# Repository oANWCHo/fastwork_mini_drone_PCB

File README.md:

# Mini Drone PCB
### This project was designed in KiCAD V9.0 
### If you don't have this program, you can find a schematic for review in the documents folder.

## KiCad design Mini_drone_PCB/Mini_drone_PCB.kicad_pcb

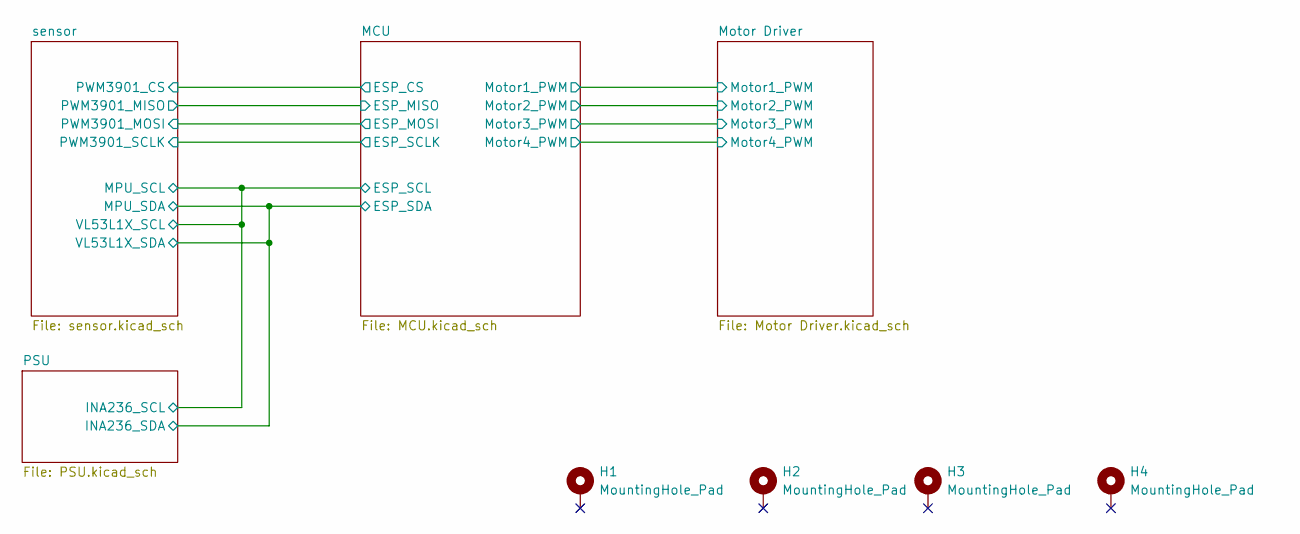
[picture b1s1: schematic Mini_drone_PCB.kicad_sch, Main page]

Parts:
H1, H2, H3, H4: MountingHole_Pad; MountingHole_2.5mm_Pad

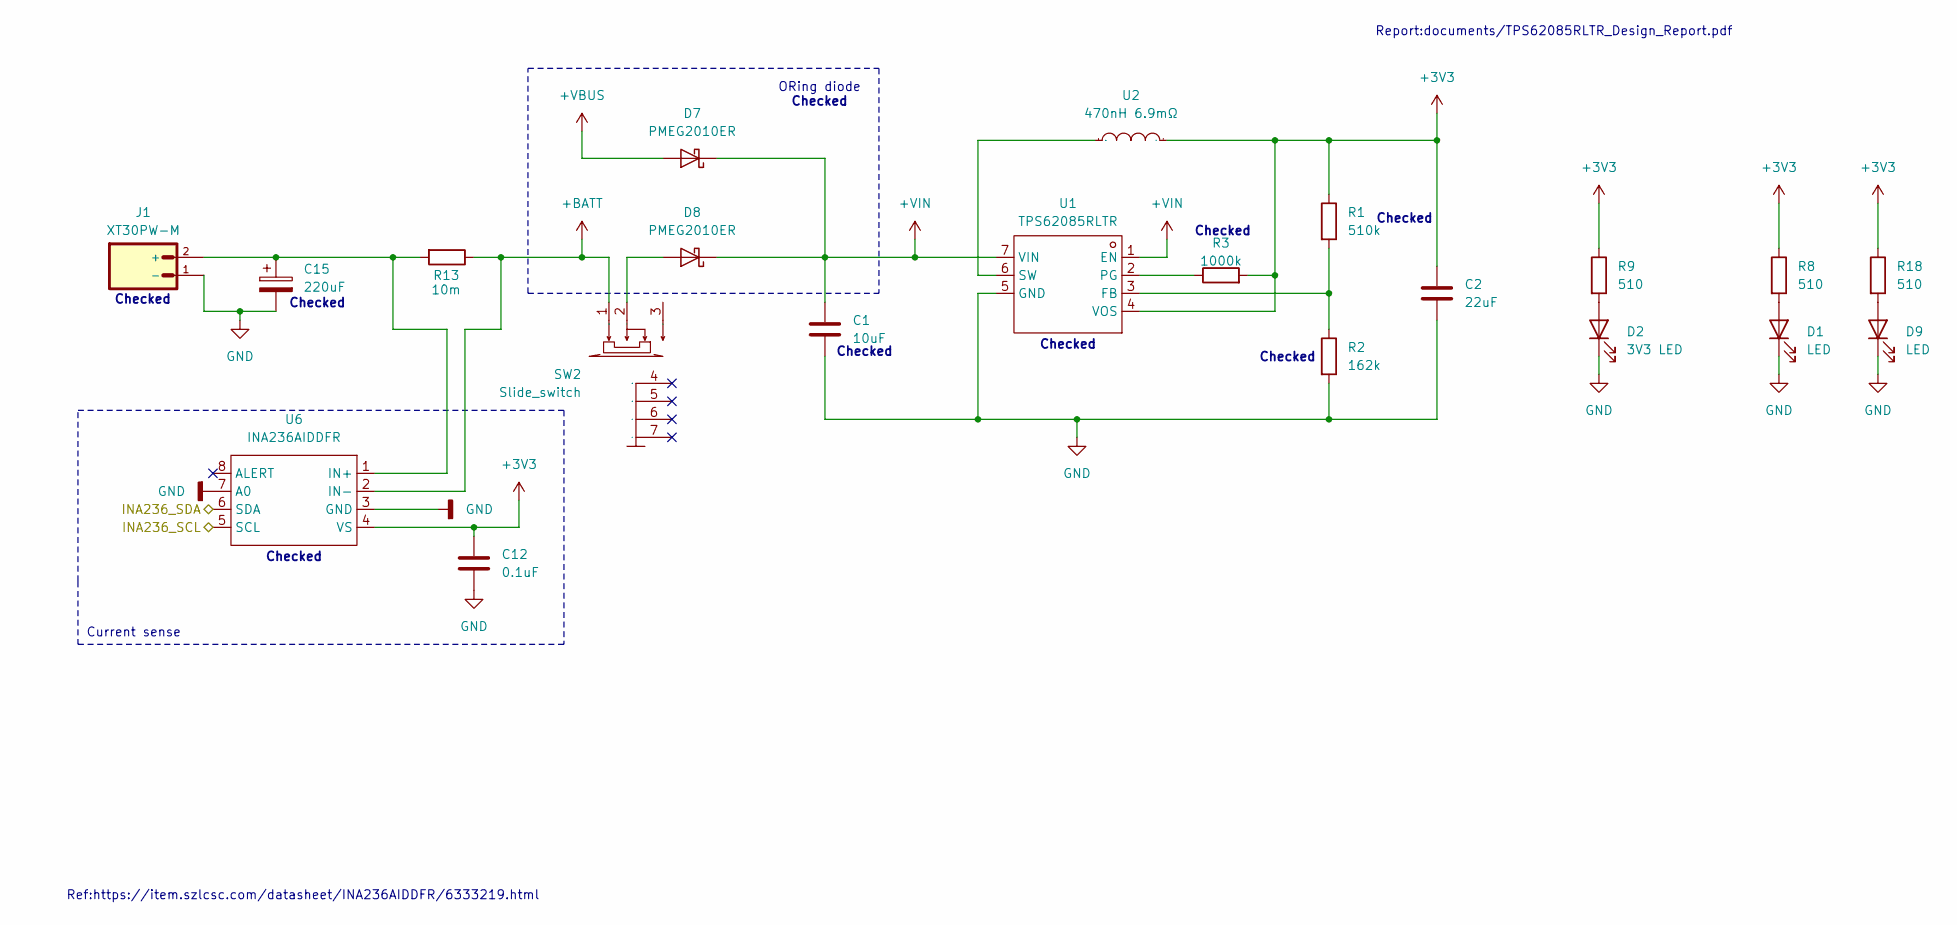
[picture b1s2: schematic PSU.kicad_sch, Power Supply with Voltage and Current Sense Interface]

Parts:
C1: 10uF; C_0402_1005Metric; LCSC Part # C15525
C2: 22uF; C_0402_1005Metric; LCSC Part # C105226
C12: 0.1uF; C_0402_1005Metric; LCSC Part # C1525
C15: 220uF; CP_Elec_6.3x5.4; LCSC Part # C72494
D1, D9: LED; LED_D3.0mm_Horizontal_O6.35mm_Z2.0mm
D2: 3V3 LED; LED_0603_1608Metric; LCSC Part # C2286
D7, D8: PMEG2010ER; Nexperia_CFP3_SOD-123W; LCSC Part # C82288
J1: XT30PW-M; AMASS_XT30PW-M; LCSC Part # C431092
R1: 510k; C_0402_1005Metric; LCSC Part # C11616
R2: 162k; C_0402_1005Metric; LCSC Part # C185462
R3: 1000k; C_0402_1005Metric; LCSC Part # C26083
R8, R9, R18: 510; C_0402_1005Metric; LCSC Part # C25123
R13: 10m; R_2512_6332Metric; LCSC Part # C105366
SW2: Slide_switch; SW-SMD_SSSS811101; Manufacturer Part SSSS811101; LCSC Part Name 1.4mm高、1.5/2.0mm行程表面贴装型开关
U1: TPS62085RLTR; VSON-7_L2.0-W2.0-P0.5-TL; Manufacturer Part TPS62085RLTR; LCSC Part Name 高效3A同步降压转换器
U2: 470nH 6.9mΩ; IND-SMD_L4.2-W4.0_SPM4030T; Manufacturer Part SPM4030T-R47M-HZ; LCSC Part Name 470nH ±20%
U6: INA236AIDDFR; SOT-23-8_L2.9-W1.6-P0.65-LS2.8-BR; Manufacturer Part INA236AIDDFR; LCSC Part Name INA236AIDDFR

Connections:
+3V3: C2.1, C12.1, R1.1, R3.2, R8.1, R9.1, R18.1, U1.4 (VOS), U2.2, U6.4 (VS); also elsewhere on the board
+BATT: R13.1, SW2.1, U6.2 (IN-); also elsewhere on the board
+VBUS: D7.2 (A); also elsewhere on the board
+VIN: C1.1, D7.1 (K), D8.1 (K), U1.1 (EN), U1.7 (VIN)
/MCU/ESP_SCL: U6.5 (SCL); also elsewhere on the board
/MCU/ESP_SDA: U6.6 (SDA); also elsewhere on the board
GND: C1.2, C2.2, C12.2, C15.2, D1.1 (K), D2.1 (K), D9.1 (K), J1.1 (-), R2.2, U1.5 (GND), U6.3 (GND), U6.7 (A0); also elsewhere on the board
unnamed: D1.2 (A), R8.2
unnamed: D2.2 (A), R9.2
unnamed: D8.2 (A), SW2.2
unnamed: D9.2 (A), R18.2
unnamed: C15.1, J1.2 (+), R13.2, U6.1 (IN+)
unnamed: R1.2, R2.1, U1.3 (FB)
unnamed: R3.1, U1.2 (PG)
unnamed: U1.6 (SW), U2.1

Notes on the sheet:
ORing diode
Checked
Current sense
Report:documents/TPS62085RLTR_Design_Report.pdf
Ref:https://item.szlcsc.com/datasheet/INA236AIDDFR/6333219.html

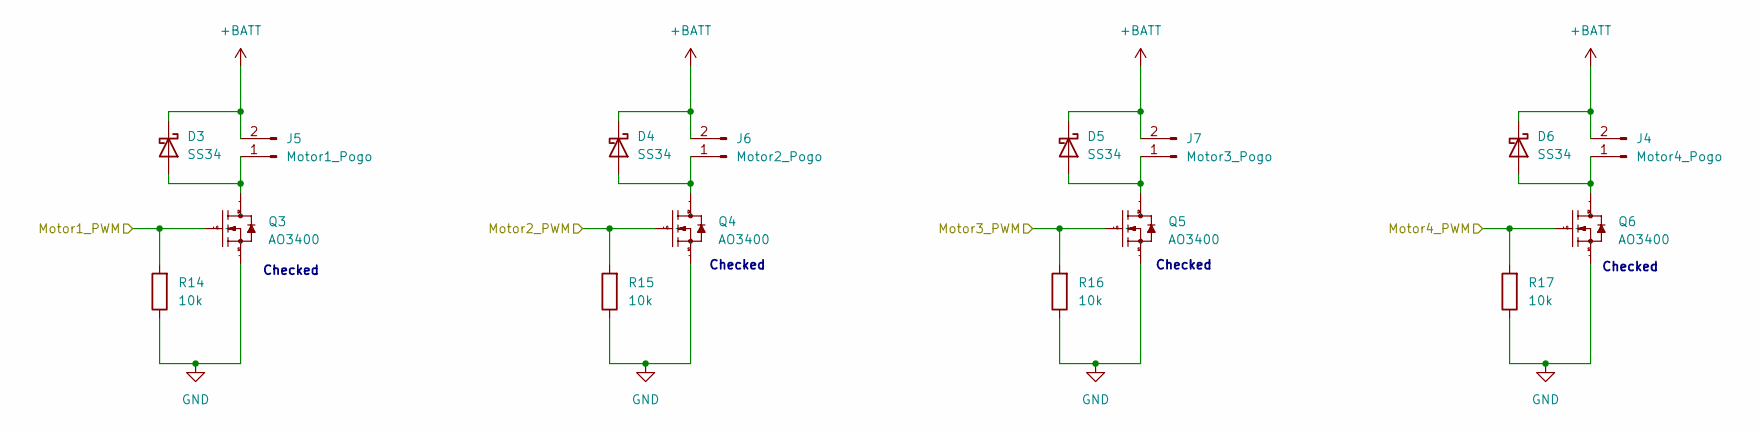
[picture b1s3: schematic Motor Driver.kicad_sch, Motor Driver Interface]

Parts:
D3, D4, D5, D6: SS34; D_SMA; LCSC Part # C8678
J4: Motor4_Pogo; POGO 2Pin Pitch 4
J5: Motor1_Pogo; POGO 2Pin Pitch 4
J6: Motor2_Pogo; POGO 2Pin Pitch 4
J7: Motor3_Pogo; POGO 2Pin Pitch 4
Q3, Q4, Q5, Q6: AO3400; SOT-23-3_L2.9-W1.3-P1.90-LS2.4-BR; Manufacturer Part AO3400; LCSC Part Name 1个N沟道 耐压:30V 电流:5.8A
R14, R15, R16, R17: 10k; C_0402_1005Metric; LCSC Part # C25531

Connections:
+BATT: D3.1 (K), D4.1 (K), D5.1 (K), D6.1 (K), J4.2, J5.2, J6.2, J7.2; also elsewhere on the board
/MCU/Motor1_PWM: Q3.1 (G), R14.2; also elsewhere on the board
/MCU/Motor2_PWM: Q4.1 (G), R15.2; also elsewhere on the board
/MCU/Motor3_PWM: Q5.1 (G), R16.2; also elsewhere on the board
/MCU/Motor4_PWM: Q6.1 (G), R17.2; also elsewhere on the board
GND: Q3.2 (S), Q4.2 (S), Q5.2 (S), Q6.2 (S), R14.1, R15.1, R16.1, R17.1; also elsewhere on the board
unnamed: D3.2 (A), J5.1, Q3.3 (D)
unnamed: D4.2 (A), J6.1, Q4.3 (D)
unnamed: D5.2 (A), J7.1, Q5.3 (D)
unnamed: D6.2 (A), J4.1, Q6.3 (D)

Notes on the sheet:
Checked

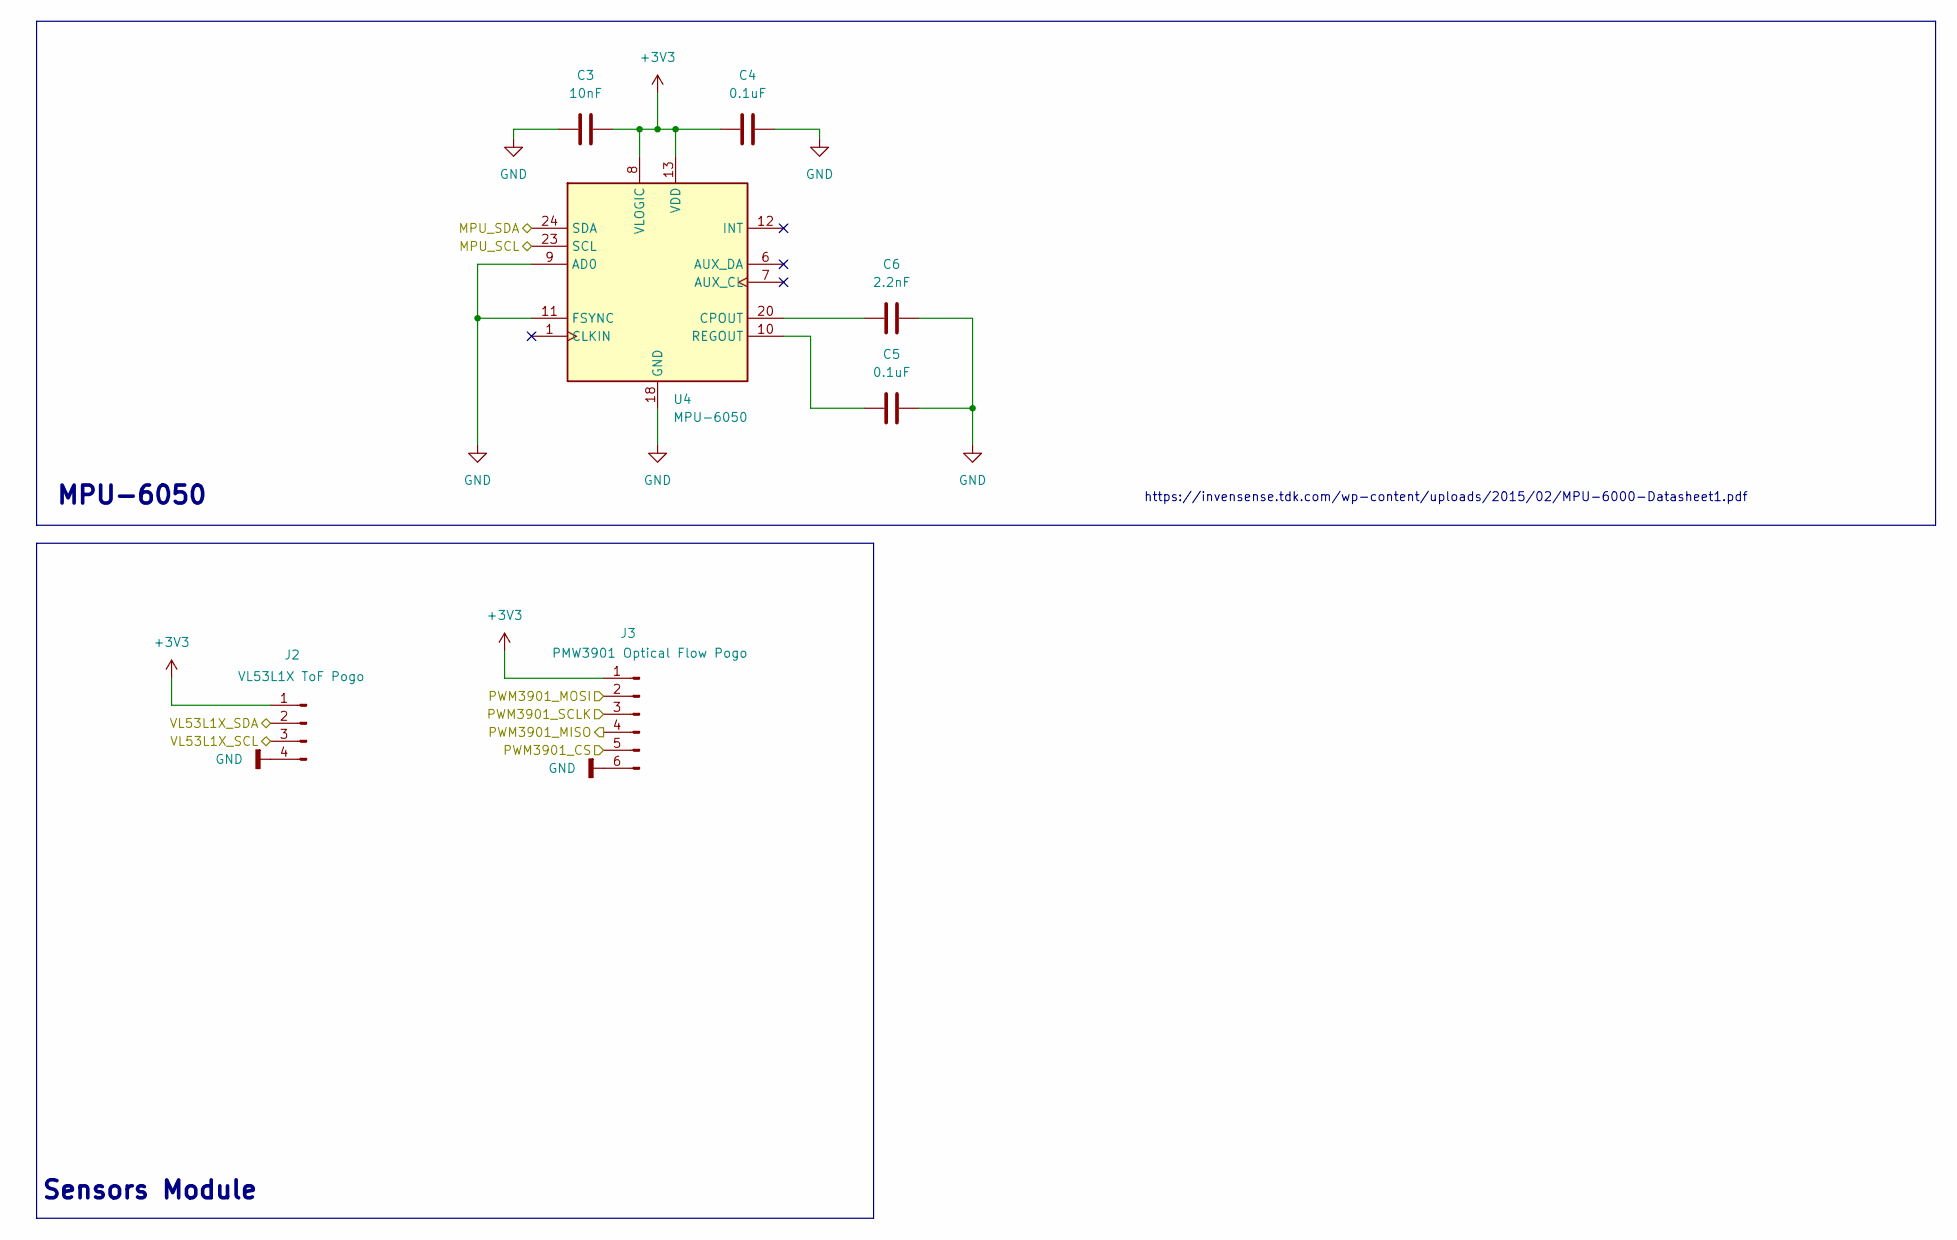
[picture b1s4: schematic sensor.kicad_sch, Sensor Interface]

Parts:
C3: 10nF; C_0402_1005Metric; LCSC Part # C15195
C4, C5: 0.1uF; C_0402_1005Metric; LCSC Part # C1525
C6: 2.2nF; C_0402_1005Metric; LCSC Part # C1531
J2: VL53L1X ToF Pogo; POGO 4Pin Pitch 2.54
J3: PMW3901 Optical Flow Pogo; POGO 6Pin Pitch 2.54
U4: MPU-6050; InvenSense_QFN-24_4x4mm_P0.5mm; LCSC Part # C24112

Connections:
+3V3: C3.1, C4.2, J2.1, J3.1, U4.8 (VLOGIC), U4.13 (VDD); also elsewhere on the board
/MCU/ESP_CS: J3.5; also elsewhere on the board
/MCU/ESP_MISO: J3.4; also elsewhere on the board
/MCU/ESP_MOSI: J3.2; also elsewhere on the board
/MCU/ESP_SCL: J2.3, U4.23 (SCL); also elsewhere on the board
/MCU/ESP_SCLK: J3.3; also elsewhere on the board
/MCU/ESP_SDA: J2.2, U4.24 (SDA); also elsewhere on the board
GND: C3.2, C4.1, C5.1, C6.1, J2.4, J3.6, U4.9 (AD0), U4.11 (FSYNC), U4.18 (GND); also elsewhere on the board
unnamed: C6.2, U4.20 (CPOUT)
unnamed: C5.2, U4.10 (REGOUT)

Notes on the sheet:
https://invensense.tdk.com/wp-content/uploads/2015/02/MPU-6000-Datasheet1.pdf
MPU-6050
Sensors Module

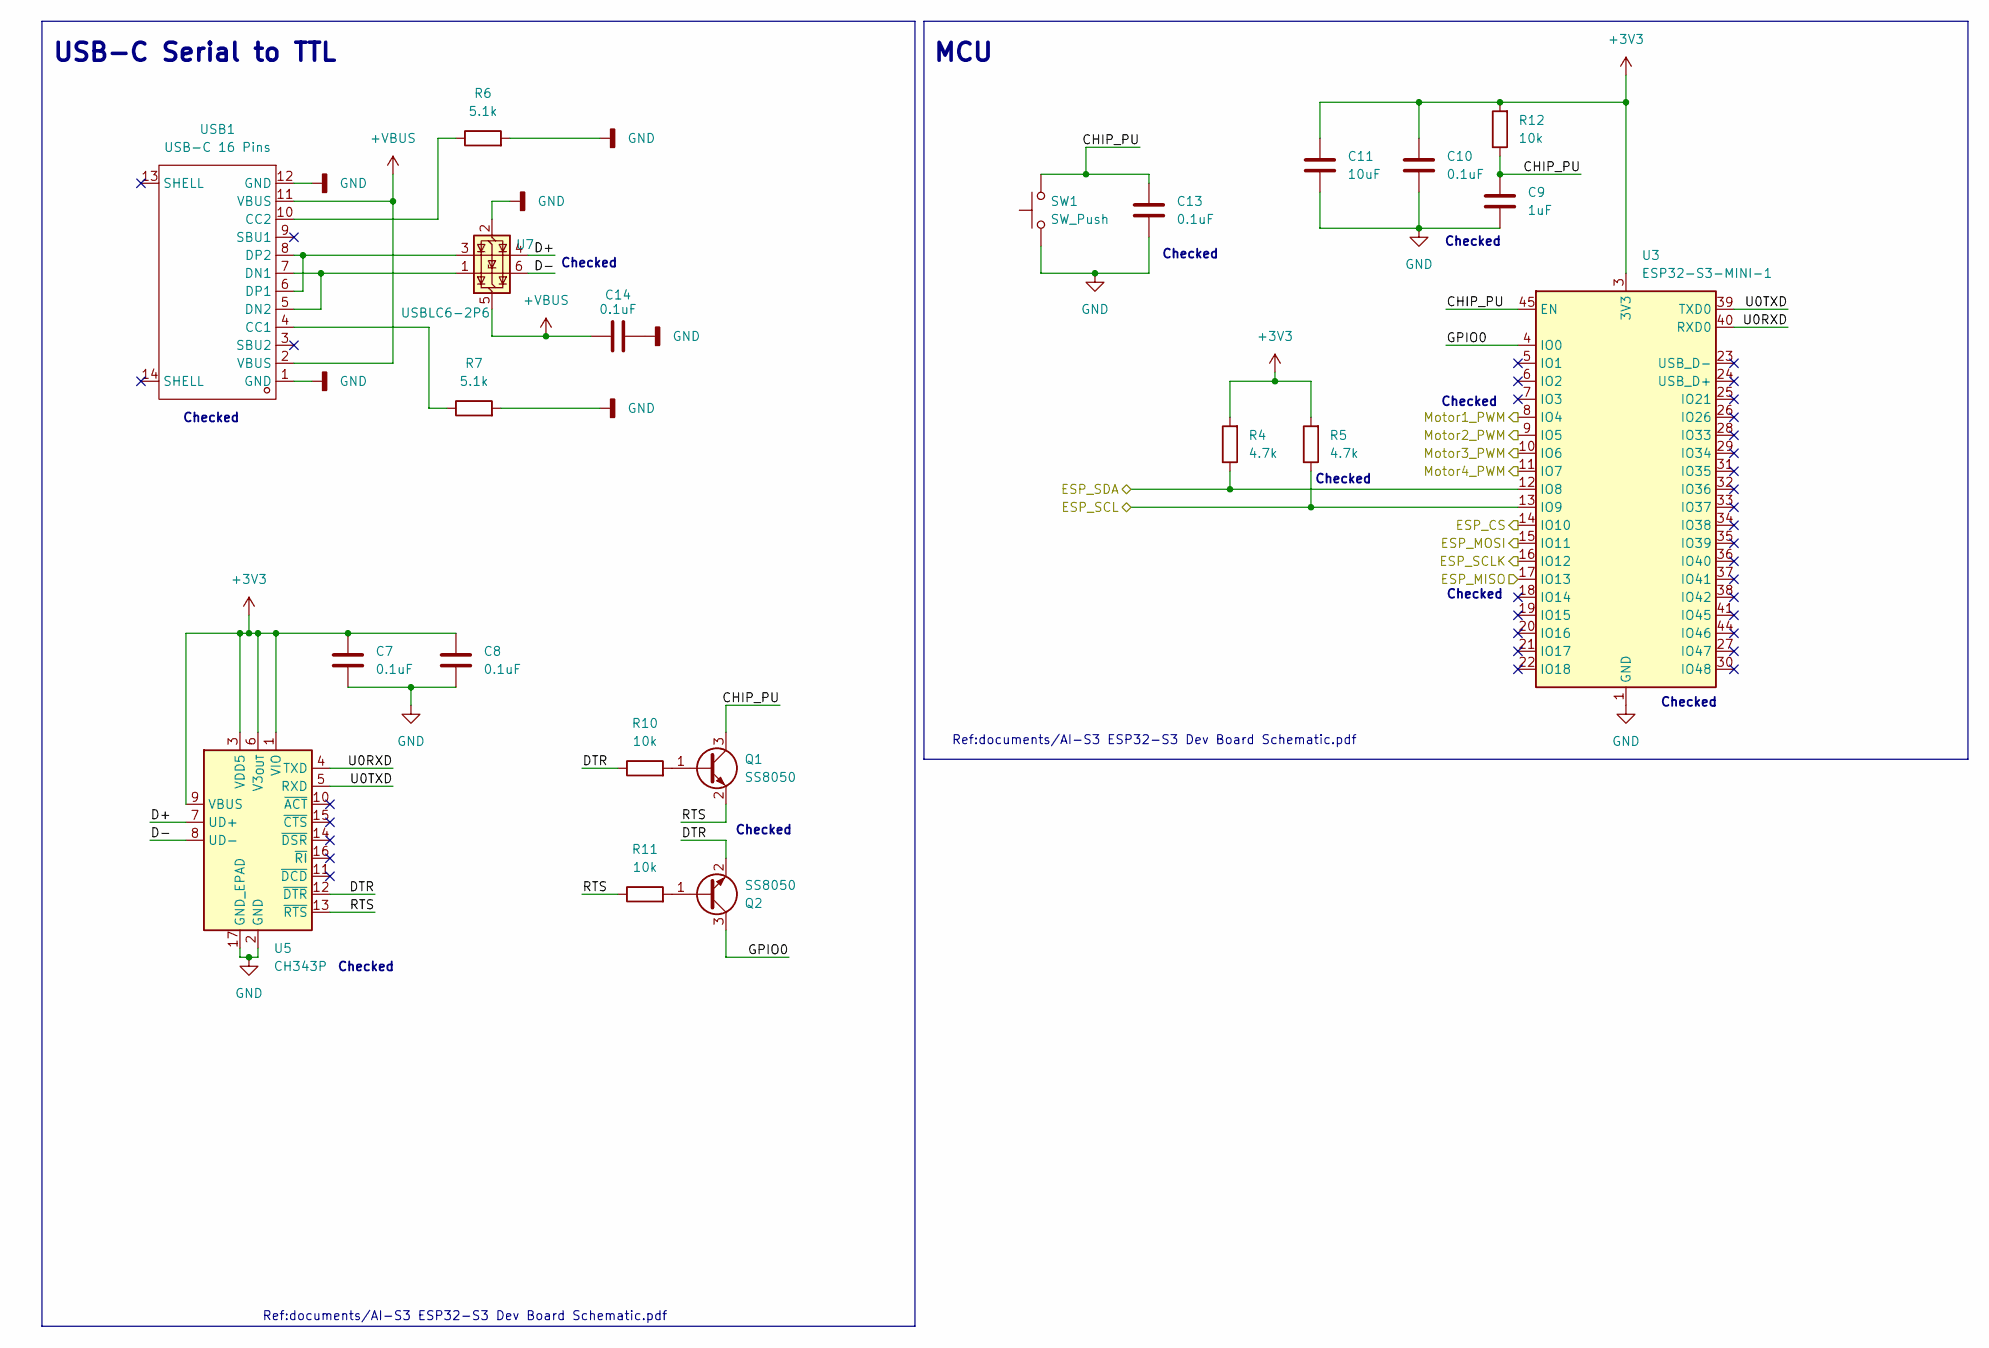
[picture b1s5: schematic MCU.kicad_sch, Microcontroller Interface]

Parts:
C7, C8, C10, C13, C14: 0.1uF; C_0402_1005Metric; LCSC Part # C1525
C9: 1uF; C_0402_1005Metric; LCSC Part # C14445
C11: 10uF; C_0402_1005Metric; LCSC Part # C15525
Q1, Q2: SS8050; SOT-23; LCSC Part # C2150
R4, R5: 4.7k; C_0402_1005Metric; LCSC Part # C25900
R6, R7: 5.1k; C_0402_1005Metric; LCSC Part # C25905
R10, R11, R12: 10k; C_0402_1005Metric; LCSC Part # C25531
SW1: SW_Push; SW_Tactile_SPST_NO_Straight_CK_PTS636Sx25SMTRLFS; LCSC Part # C318938
U3: ESP32-S3-MINI-1; ESP32-S2-MINI-1; LCSC Part # C2913206
U5: CH343P; WCH_QFN-16-1EP_3x3mm_P0.5mm_EP1.8x1.8mm; LCSC Part # C2846043
U7: USBLC6-2P6; SOT-666; LCSC Part # C15999
USB1: USB-C 16 Pins; USB-C-SMD_TYPE-C-16PIN; Manufacturer Part TYPE-C 16PIN 2MD(073); LCSC Part Name Type-C 母 卧贴

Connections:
+3V3: C7.1, C8.1, C10.1, C11.1, R4.2, R5.2, R12.2, U3.3 (3V3), U5.1 (VIO), U5.3 (VDD5), U5.6 (V3_{OUT}), U5.9 (VBUS); also elsewhere on the board
+VBUS: C14.1, U7.5 (VBUS), USB1.2 (VBUS), USB1.11 (VBUS); also elsewhere on the board
/MCU/CHIP_PU: C9.1, C13.1, Q1.3 (C), R12.1, SW1.2, U3.45 (EN)
/MCU/D+: U5.7 (UD+), U7.4 (I/O2)
/MCU/D-: U5.8 (UD-), U7.6 (I/O1)
/MCU/DTR: Q2.2 (E), R10.1, U5.12 (~DTR)
/MCU/ESP_CS: U3.14 (IO10); also elsewhere on the board
/MCU/ESP_MISO: U3.17 (IO13); also elsewhere on the board
/MCU/ESP_MOSI: U3.15 (IO11); also elsewhere on the board
/MCU/ESP_SCL: R5.1, U3.13 (IO9); also elsewhere on the board
/MCU/ESP_SCLK: U3.16 (IO12); also elsewhere on the board
/MCU/ESP_SDA: R4.1, U3.12 (IO8); also elsewhere on the board
/MCU/GPIO0: Q2.3 (C), U3.4 (IO0)
/MCU/Motor1_PWM: U3.8 (IO4); also elsewhere on the board
/MCU/Motor2_PWM: U3.9 (IO5); also elsewhere on the board
/MCU/Motor3_PWM: U3.10 (IO6); also elsewhere on the board
/MCU/Motor4_PWM: U3.11 (IO7); also elsewhere on the board
/MCU/RTS: Q1.2 (E), R11.1, U5.13 (~RTS)
/MCU/U0RXD: U3.40 (RXD0), U5.4 (TXD)
/MCU/U0TXD: U3.39 (TXD0), U5.5 (RXD)
GND: C7.2, C8.2, C9.2, C10.2, C11.2, C13.2, C14.2, R6.2, R7.2, SW1.1, U3.1 (GND), U3.2 (GND), U3.42 (GND), U3.43 (GND), U3.46 (GND), U3.47 (GND), U3.48 (GND), U3.49 (GND), U3.50 (GND), U3.51 (GND), U3.52 (GND), U3.53 (GND), U3.54 (GND), U3.55 (GND), U3.56 (GND), U3.57 (GND), U3.58 (GND), U3.59 (GND), U3.60 (GND), U3.61 (GND), U3.62 (GND), U3.63 (GND), U3.64 (GND), U3.65 (GND), U5.2 (GND), U5.17 (GND_EPAD), U7.2 (GND), USB1.1 (GND), USB1.12 (GND); also elsewhere on the board
unnamed: Q1.1 (B), R10.2
unnamed: Q2.1 (B), R11.2
unnamed: R7.1, USB1.4 (CC1)
unnamed: R6.1, USB1.10 (CC2)
unnamed: U7.1 (I/O1), USB1.5 (DN2), USB1.7 (DN1)
unnamed: U7.3 (I/O2), USB1.6 (DP1), USB1.8 (DP2)

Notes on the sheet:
Ref:documents/AI-S3 ESP32-S3 Dev Board Schematic.pdf
Checked
MCU
USB-C Serial to TTL

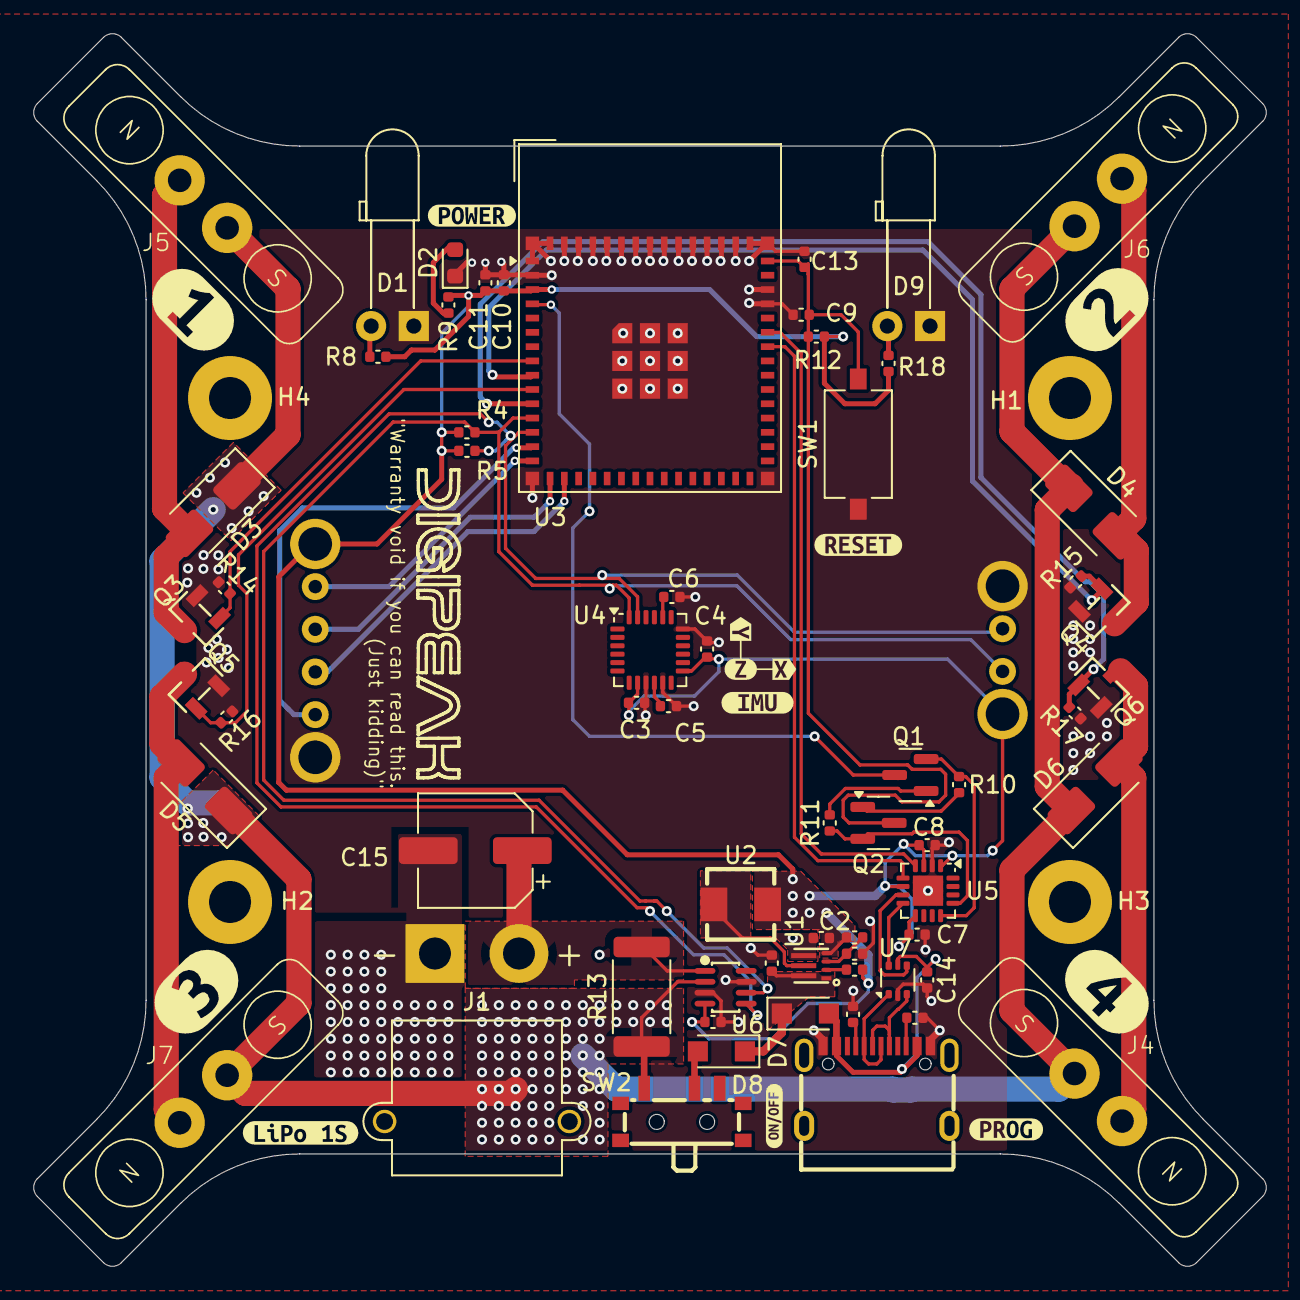
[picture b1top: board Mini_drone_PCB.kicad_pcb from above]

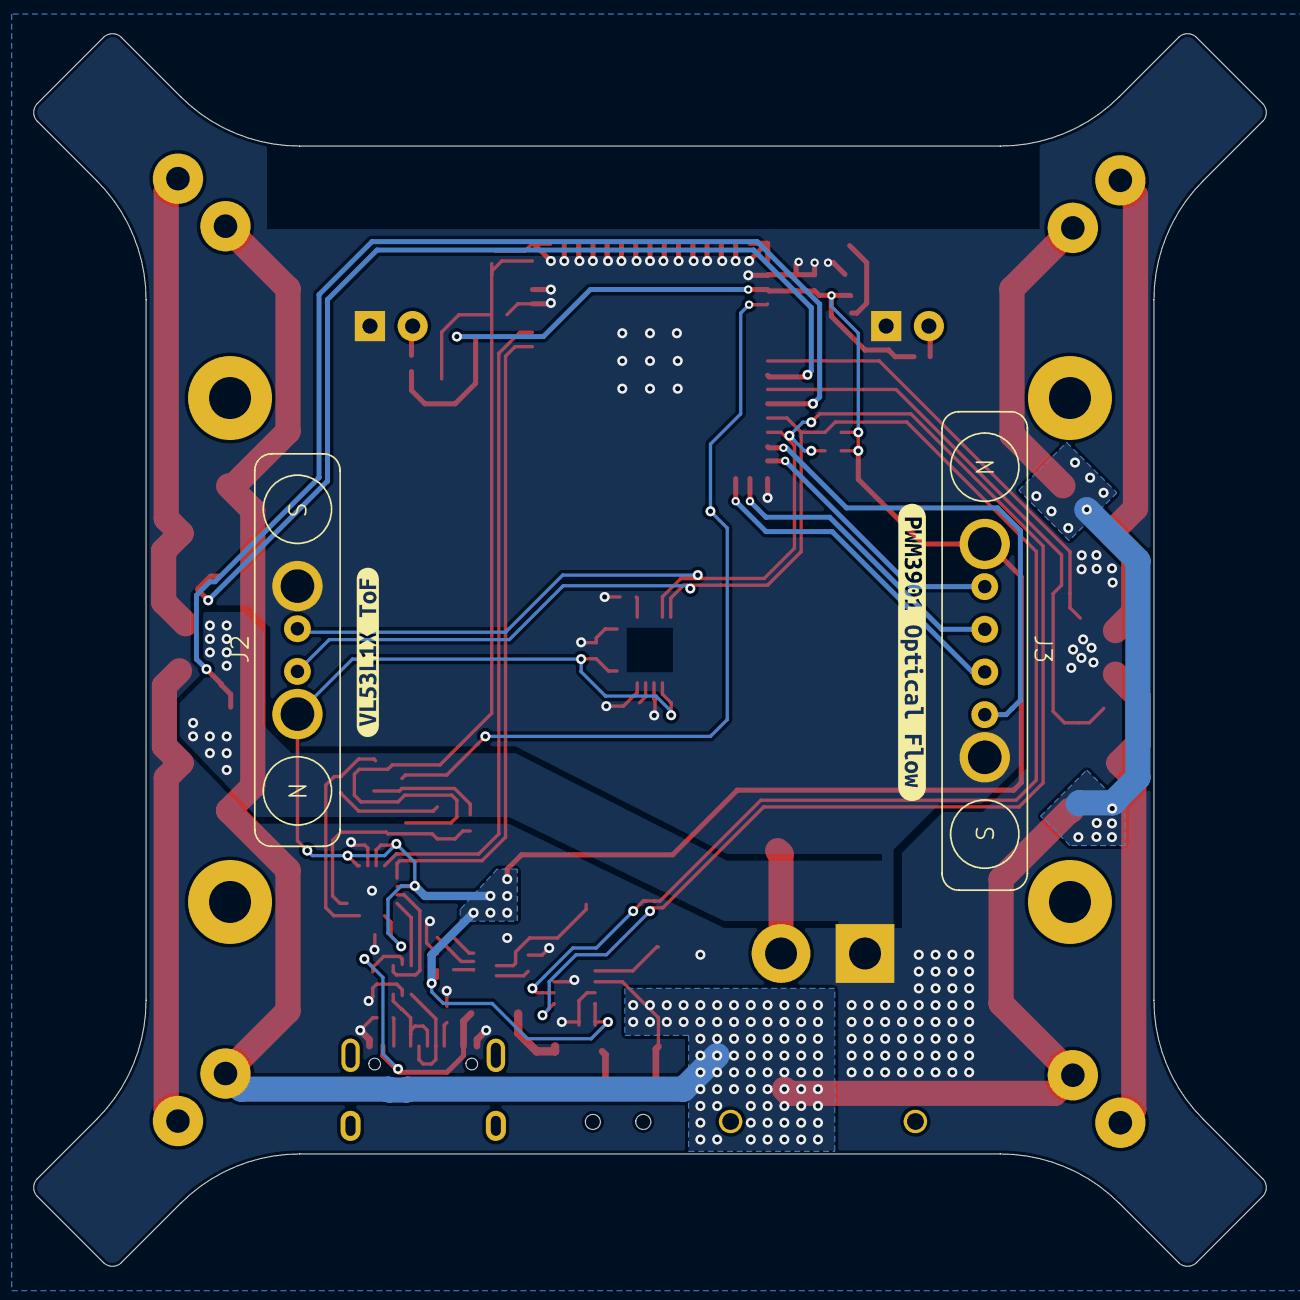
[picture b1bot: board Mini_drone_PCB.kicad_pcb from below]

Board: 2 copper layers, 73.4 x 73.4 mm, 84 parts (4 on the bottom side), 43 nets.

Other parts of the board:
kibuzzard-696EF0B2: G***; kibuzzard-696EF0B2
kibuzzard-696EF1CC: G***; kibuzzard-696EF1CC
kibuzzard-696EF1EE: G***; kibuzzard-696EF1EE
kibuzzard-696EF12B: G***; kibuzzard-696EF12B
kibuzzard-696EF14F: G***; kibuzzard-696EF14F
kibuzzard-696EF15F: G***; kibuzzard-696EF15F
kibuzzard-696EF46D: G***; kibuzzard-696EF46D
kibuzzard-696EF072: G***; kibuzzard-696EF072
kibuzzard-696EF142: G***; kibuzzard-696EF142
kibuzzard-696EF202: G***; kibuzzard-696EF202
kibuzzard-696EF488: G***; kibuzzard-696EF488
kibuzzard-696EFAC1: G***; kibuzzard-696EFAC1
kibuzzard-696EFAE6: G***; kibuzzard-696EFAE6
kibuzzard-696EFB3D: G***; kibuzzard-696EFB3D
kibuzzard-696EFB18: G***; kibuzzard-696EFB18

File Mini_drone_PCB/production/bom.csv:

Designator,Footprint,Quantity,Value,LCSC Part #
"C1, C11",0402,2,10uF,C15525
"C10, C12, C13, C14, C4, C5, C7, C8",0402,8,0.1uF,C1525
C15,CP_Elec_6.3x5.4,1,220uF,
C2,0402,1,22uF,C105226
C3,0402,1,10nF,C15195 
C6,0402,1,2.2nF,C1531 
C9,0402,1,1uF,C14445 
"D1, D9",LED_D3.0mm_Horizontal_O6.35mm_Z2.0mm,2,LED,C86881
D2,0603,1,3V3 LED,C2286
"D3, D4, D5, D6",D_SMA,4,SS34,C8678
"D7, D8",Nexperia_CFP3_SOD-123W,2,PMEG2010ER,C82288 
J1,AMASS_XT30PW-M,1,XT30PW-M,C431092
J2,POGO 4Pin Pitch 2.54,1,VL53L1X ToF Pogo,
J3,POGO 6Pin Pitch 2.54,1,PMW3901 Optical Flow Pogo,
J4,POGO 2Pin Pitch 4,1,Motor4_Pogo,
J5,POGO 2Pin Pitch 4,1,Motor1_Pogo,
J6,POGO 2Pin Pitch 4,1,Motor2_Pogo,
J7,POGO 2Pin Pitch 4,1,Motor3_Pogo,
"Q1, Q2",SOT-23,2,SS8050,C2150
"Q3, Q4, Q5, Q6",SOT-23-3_L2.9-W1.3-P1.90-LS2.4-BR,4,AO3400,C20917 
R1,0402,1,510k,C11616
"R10, R11, R12, R14, R15, R16, R17",0402,7,10k,C25531
R13,2512,1,10m,C105366 
"R18, R8, R9",0402,3,510,C25123
R2,0402,1,162k,C185462 
R3,0402,1,1000k,C26083 
"R4, R5",0402,2,4.7k,C25900
"R6, R7",0402,2,5.1k,C25905
SW1,SW_Tactile_SPST_NO_Straight_CK_PTS636Sx25SMTRLFS,1,SW_Push,C318938
SW2,SW-SMD_SSSS811101,1,Slide_switch,C109335
U1,VSON-7_L2.0-W2.0-P0.5-TL,1,TPS62085RLTR,C130072
U2,IND-SMD_L4.2-W4.0_SPM4030T,1,470nH 6.9mΩ,C531455
U3,ESP32-S2-MINI-1,1,ESP32-S3-MINI-1,C2913206 
U4,InvenSense_QFN-24_4x4mm_P0.5mm,1,MPU-6050,C24112
U5,WCH_QFN-16-1EP_3x3mm_P0.5mm_EP1.8x1.8mm,1,CH343P,C2846043
U6,SOT-23-8_L2.9-W1.6-P0.65-LS2.8-BR,1,INA236AIDDFR,C5443912 
U7,SOT-666,1,USBLC6-2P6,C15999 
USB1,USB-C-SMD_TYPE-C-16PIN,1,USB-C 16 Pins,C2765186

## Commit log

2026-01-16 First_Draft
2026-01-16 Little fix and add documents
2026-01-16 more info
2026-01-18 fix sch
2026-01-18 update_sch_and_PCB
2026-01-20 Route_Finished
2026-01-21 Verified and Finished
2026-01-21 improve antenna area
2026-01-22 antenna improve
